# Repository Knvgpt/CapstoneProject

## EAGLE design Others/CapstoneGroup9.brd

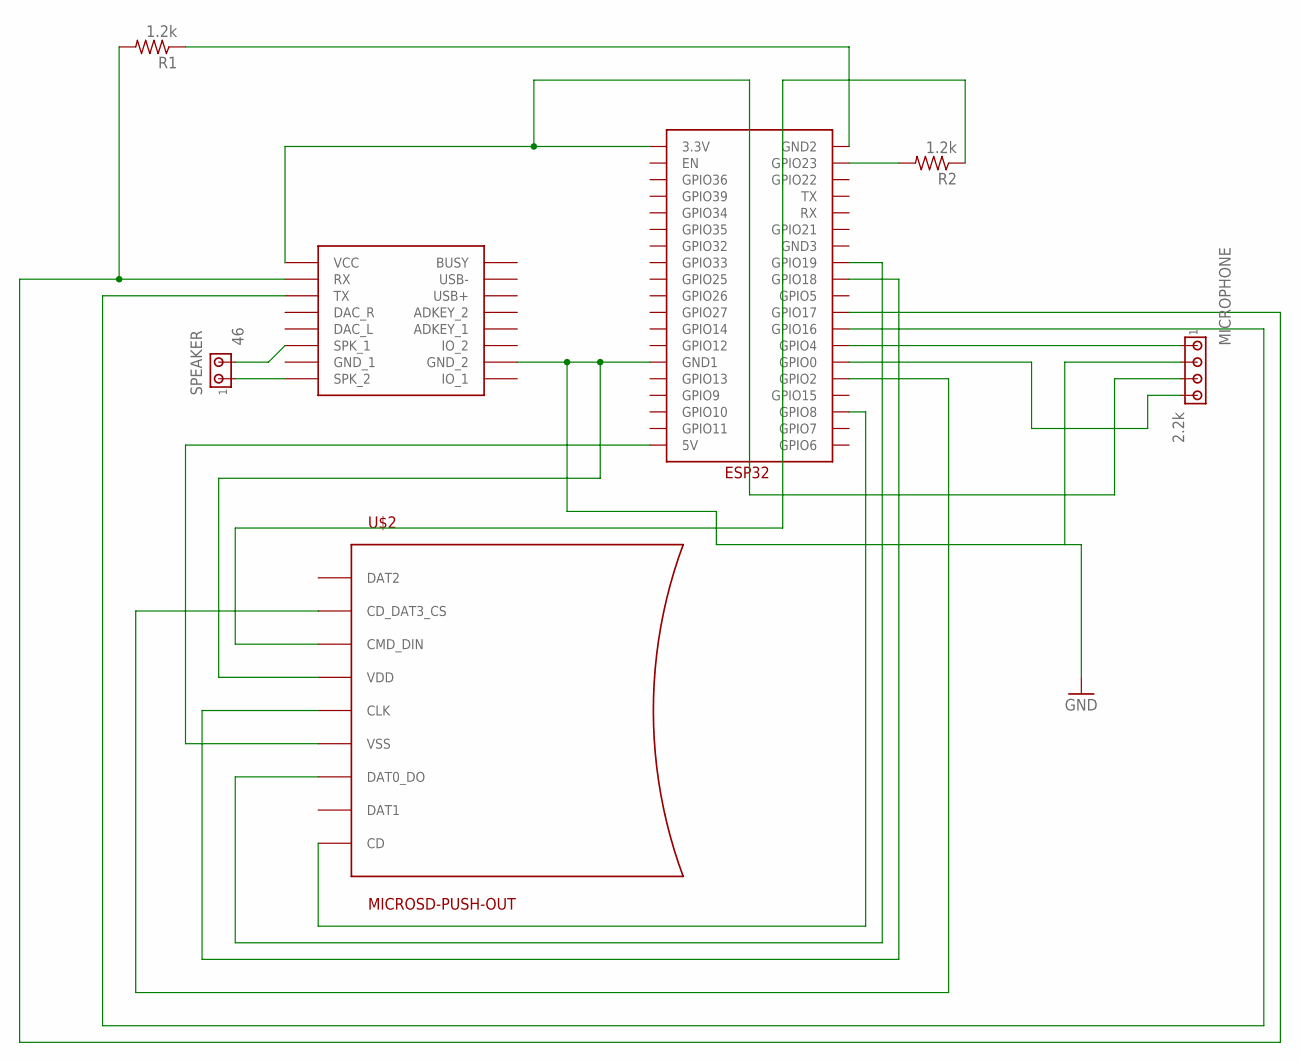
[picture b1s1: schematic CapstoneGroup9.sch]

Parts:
DFPLAYERMINI: DFPLAYER
MICROPHONE: 2.2k; 10X04MTA
R1, R2: 1.2k; 0207/10
SPEAKER: 46; 10X02MTA
U$1: ESP32
U$2: MICROSD-PUSH-OUT

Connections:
GND: DFPLAYERMINI.GND_2, MICROPHONE.2, U$1.GND1, U$2.4 (VDD)
unnamed: DFPLAYERMINI.SPK2 (SPK_2), SPEAKER.1
unnamed: DFPLAYERMINI.SPK1 (SPK_1), SPEAKER.2
unnamed: DFPLAYERMINI.VCC, MICROPHONE.3, U$1.3.3V
unnamed: DFPLAYERMINI.RX, R1.2, U$1.GPIO17
unnamed: R2.2, U$1.GPIO23
unnamed: DFPLAYERMINI.TX, U$1.GPIO16
unnamed: R1.1, U$1.GND2
unnamed: MICROPHONE.1, U$1.GPIO4
unnamed: MICROPHONE.4, U$1.GPIO0
unnamed: U$1.5V, U$2.6 (VSS), U$2.G1 (VSS), U$2.G2 (VSS), U$2.G3 (VSS), U$2.G4 (VSS)
unnamed: U$1.GPIO2, U$2.2 (CD_DAT3_CS)
unnamed: U$1.GPIO18, U$2.5 (CLK)
unnamed: U$1.GPIO8, U$2.CD
unnamed: R2.1, U$2.3 (CMD_DIN)
unnamed: U$1.GPIO19, U$2.7 (DAT0_DO)

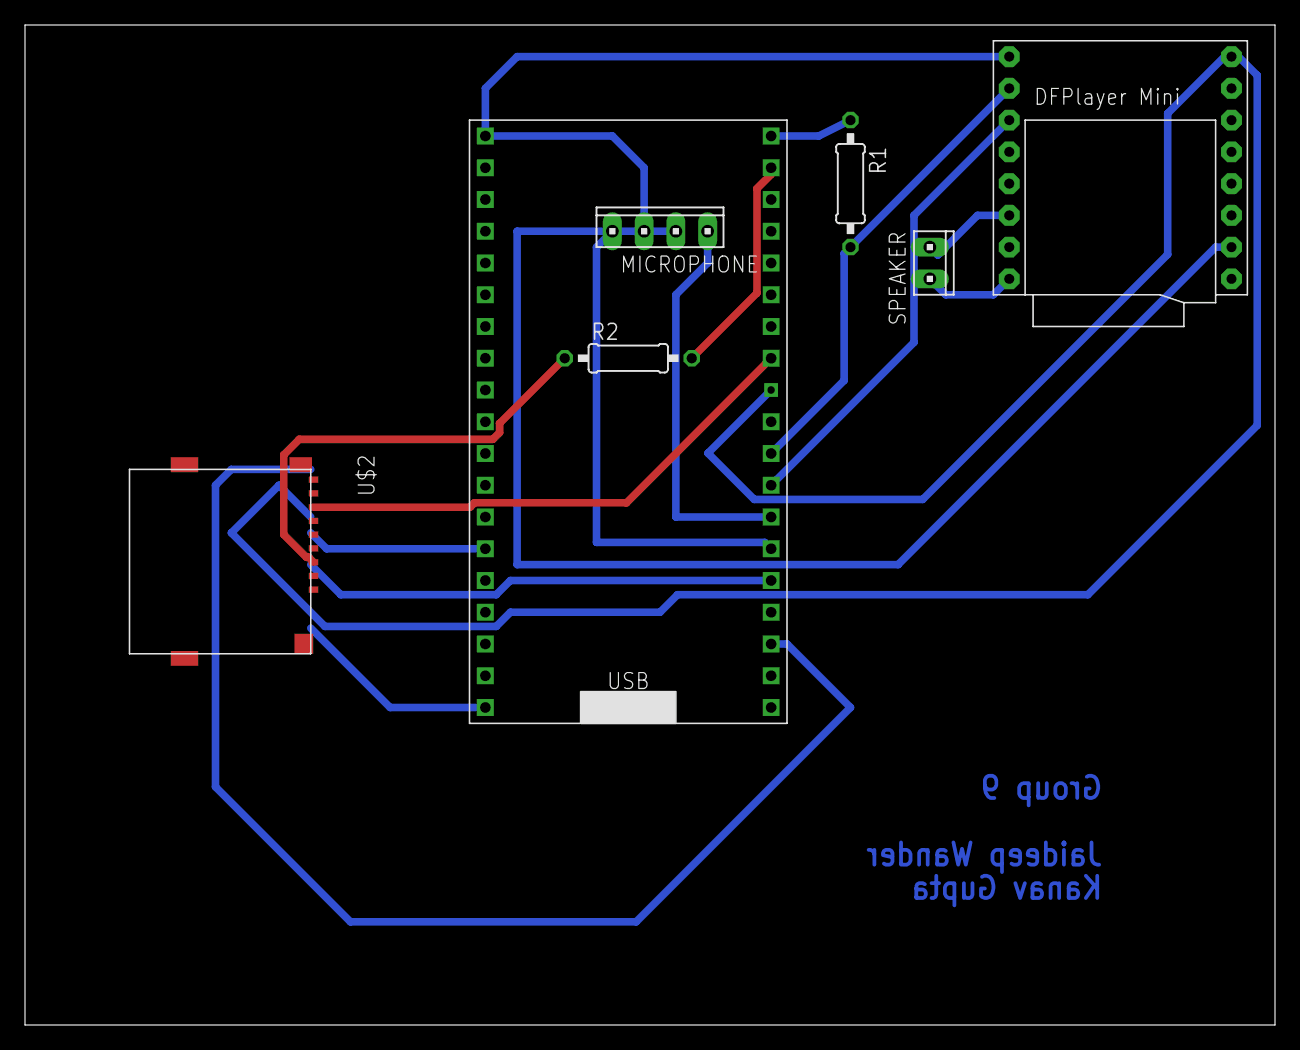
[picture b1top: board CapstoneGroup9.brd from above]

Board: 2 copper layers, 100.0 x 80.0 mm, 7 parts (0 on the bottom side), 16 nets.

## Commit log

2024-04-09 initial and final commit
